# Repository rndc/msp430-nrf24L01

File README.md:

MSP430 nRF24L01
===============

This is just a minimalist MSP430G2553 board with nRF24L01 header. All components are through hole.

Note: You should consider changing the trace width on the header before etching if the clearance is too close.

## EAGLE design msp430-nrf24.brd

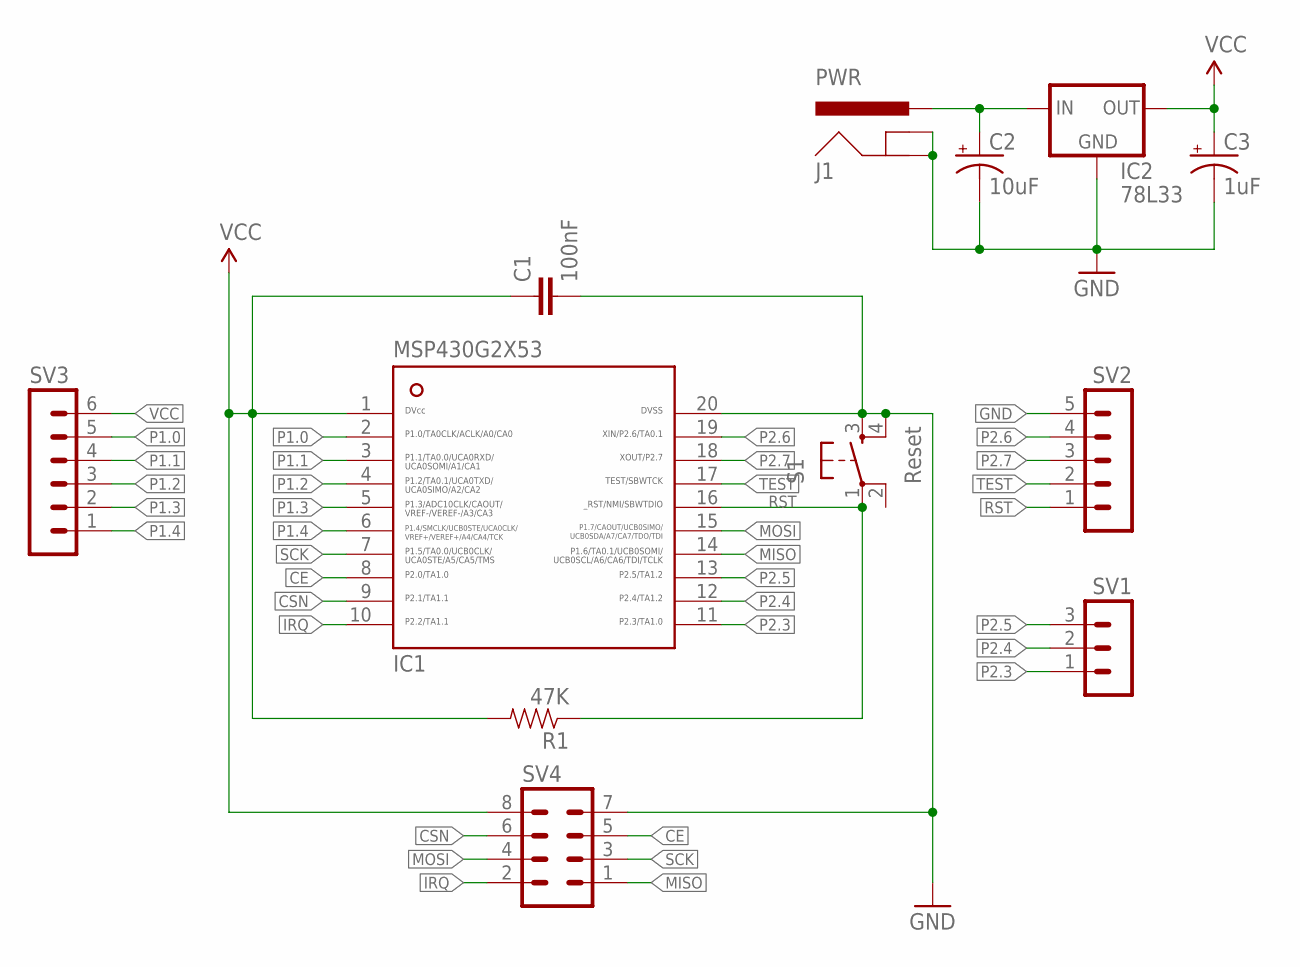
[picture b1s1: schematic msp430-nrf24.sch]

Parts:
C1: 100nF; CAP-PTH-SMALL-KIT
C2: 10uF; CPOL-RADIAL-10UF-25V
C3: 1uF; CPOL-RADIAL-10UF-25V
IC1: MSP430G2X53-20N20; N20
IC2: 78L33; TO-92
J1: PWR; POWER_JACK_PTH
R1: 47K; AXIAL-0.3-KIT
S1: Reset; TACTILE-PTH
SV1: MA03-1
SV2: MA05-1
SV3: MA06-1
SV4: MA04-2

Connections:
CE: IC1.8, SV4.5
CSN: IC1.9, SV4.6
GND: C1.2, C2.2 (-), C3.2 (-), IC1.20, IC2.1 (GND), J1.GND, J1.GNDBREAK, S1.3, S1.4, SV2.5, SV4.7
IRQ: IC1.10, SV4.2
MISO: IC1.14, SV4.1
MOSI: IC1.15, SV4.4
unnamed: C2.1 (+), IC2.2 (IN), J1.PWR
P1.0: IC1.2, SV3.5
P1.1: IC1.3, SV3.4
P1.2: IC1.4, SV3.3
P1.3: IC1.5, SV3.2
P1.4: IC1.6, SV3.1
P2.3: IC1.11, SV1.1
P2.4: IC1.12, SV1.2
P2.5: IC1.13, SV1.3
P2.6: IC1.19, SV2.4
P2.7: IC1.18, SV2.3
RST: IC1.16, R1.P$1 (1), S1.1, SV2.1
SCK: IC1.7, SV4.3
TEST: IC1.17, SV2.2
VCC: C1.1, C3.1 (+), IC1.1, IC2.3 (OUT), R1.P$2 (2), SV3.6, SV4.8

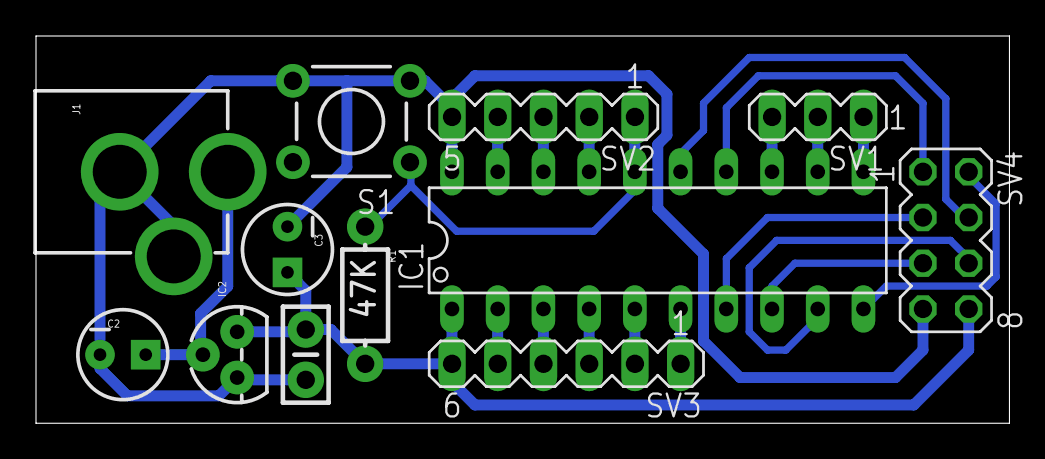
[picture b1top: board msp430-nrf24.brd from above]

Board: 2 copper layers, 54.1 x 21.5 mm, 12 parts (0 on the bottom side), 21 nets.

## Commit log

2014-10-04 Added board picture
2014-10-04 CERN Open Hardware Licence v1.2
2014-10-05 Fixed routing and dc barrel jack
2014-10-06 Better ground plane
2014-10-06 Fixed routing
2015-02-04 :new: Change board layout

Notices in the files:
parts and their libraries:
SparkFun-Capacitors: Licensing: Creative Commons ShareAlike 4.0 International - https://creativecommons.org/licenses/by-sa/4.0
